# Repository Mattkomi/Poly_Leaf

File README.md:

# Poly_Leaf
PFE 2024-2025 Polytech SIR, projet Visio
Ce projet vise à développer un système de Stream Deck permettant de centraliser et d'optimiser la gestion des équipements situés dans des salles spécifiques. 
L'objectif est de créer un dispositif ergonomique et intuitif regroupant toutes les connexions HDMI, RJ45, et USB des différents équipements dans un système unifié, 
tout en offrant des fonctionnalités avancées comme la création de macros personnalisées.

Le système est conçu pour :

Simplifier la gestion des équipements grâce à une interface centralisée.
Automatiser des tâches fréquentes, comme l'affichage des participants sur l'écran de retour ou le lancement d'applications utilisées régulièrement.
Reproduire, tout en innovant, les fonctionnalités de l'interface StarLeaf.
Ce projet a été réalisé dans le cadre du PFE VISIO de la filière Polytech SIR par :

Vincent Goossens
Matthieu Komisarek

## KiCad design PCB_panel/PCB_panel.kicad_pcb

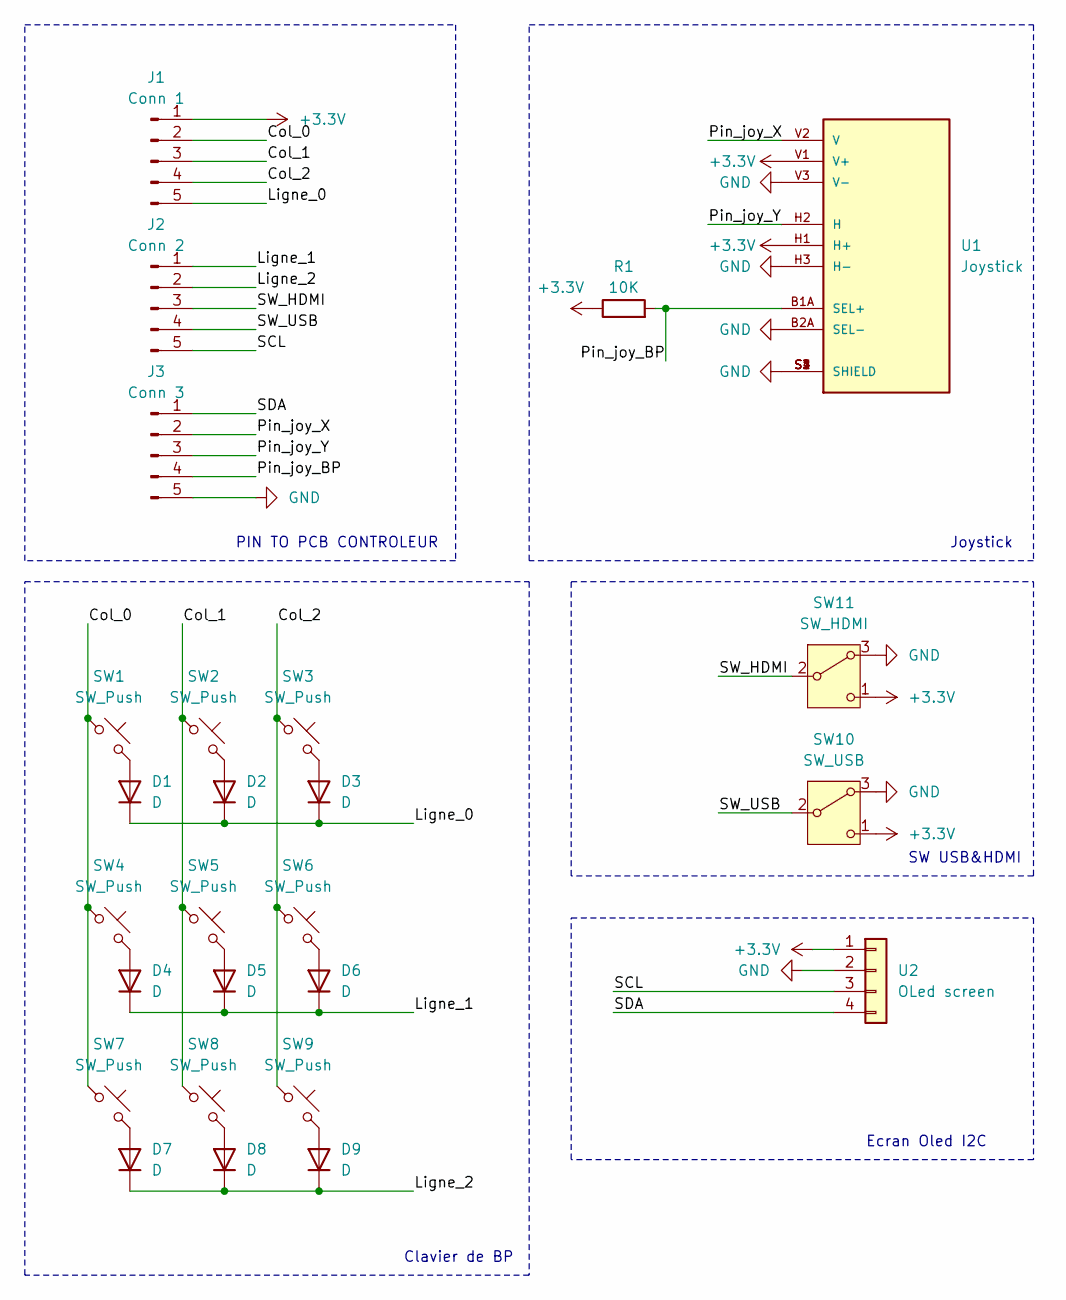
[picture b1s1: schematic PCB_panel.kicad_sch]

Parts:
D1, D2, D3, D4, D5, D6, D7, D8, D9: D; D_A-405_P10.16mm_Horizontal
J1: Conn 1; Molex_Micro-Fit_3.0_43650-0515_1x05_P3.00mm_Vertical
J2: Conn 2; Molex_Micro-Fit_3.0_43650-0515_1x05_P3.00mm_Vertical
J3: Conn 3; Molex_Micro-Fit_3.0_43650-0515_1x05_P3.00mm_Vertical
R1: 10K; R_Axial_DIN0207_L6.3mm_D2.5mm_P10.16mm_Horizontal
SW1, SW2, SW3, SW4, SW5, SW6, SW7, SW8, SW9: SW_Push; PVA1 OA H1 1.2N V2
SW10: SW_USB; PinHeader_1x03_P2.54mm_Vertical
SW11: SW_HDMI; PinHeader_1x03_P2.54mm_Vertical
U1: Joystick; XDCR_COM-09032; PARTREV N/A
U2: OLed screen; PinSocket_1x04_P2.54mm_Vertical

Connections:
+3.3V: J1.1, R1.1, SW10.1 (C), SW11.1 (C), U1.H1 (H+), U1.V1 (V+), U2.1
/Col_0: J1.2, SW1.1, SW4.1, SW7.1
/Col_1: J1.3, SW2.1, SW5.1, SW8.1
/Col_2: J1.4, SW3.1, SW6.1, SW9.1
/Ligne_0: D1.1 (K), D2.1 (K), D3.1 (K), J1.5
/Ligne_1: D4.1 (K), D5.1 (K), D6.1 (K), J2.1
/Ligne_2: D7.1 (K), D8.1 (K), D9.1 (K), J2.2
/Pin_joy_BP: J3.4, R1.2, U1.B1A (SEL+)
/Pin_joy_X: J3.2, U1.V2 (V)
/Pin_joy_Y: J3.3, U1.H2 (H)
/SCL: J2.5, U2.3
/SDA: J3.1, U2.4
/SW_HDMI: J2.3, SW11.2 (B)
/SW_USB: J2.4, SW10.2 (B)
GND: J3.5, SW10.3 (A), SW11.3 (A), U1.B2A (SEL-), U1.H3 (H-), U1.S1 (SHIELD), U1.S2 (SHIELD), U1.S3 (SHIELD), U1.S4 (SHIELD), U1.V3 (V-), U2.2
unnamed: D1.2 (A), SW1.2
unnamed: D2.2 (A), SW2.2
unnamed: D3.2 (A), SW3.2
unnamed: D4.2 (A), SW4.2
unnamed: D5.2 (A), SW5.2
unnamed: D6.2 (A), SW6.2
unnamed: D7.2 (A), SW7.2
unnamed: D8.2 (A), SW8.2
unnamed: D9.2 (A), SW9.2

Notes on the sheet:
Ecran Oled I2C
SW USB&HDMI
Joystick
PIN TO PCB CONTROLEUR
Clavier de BP

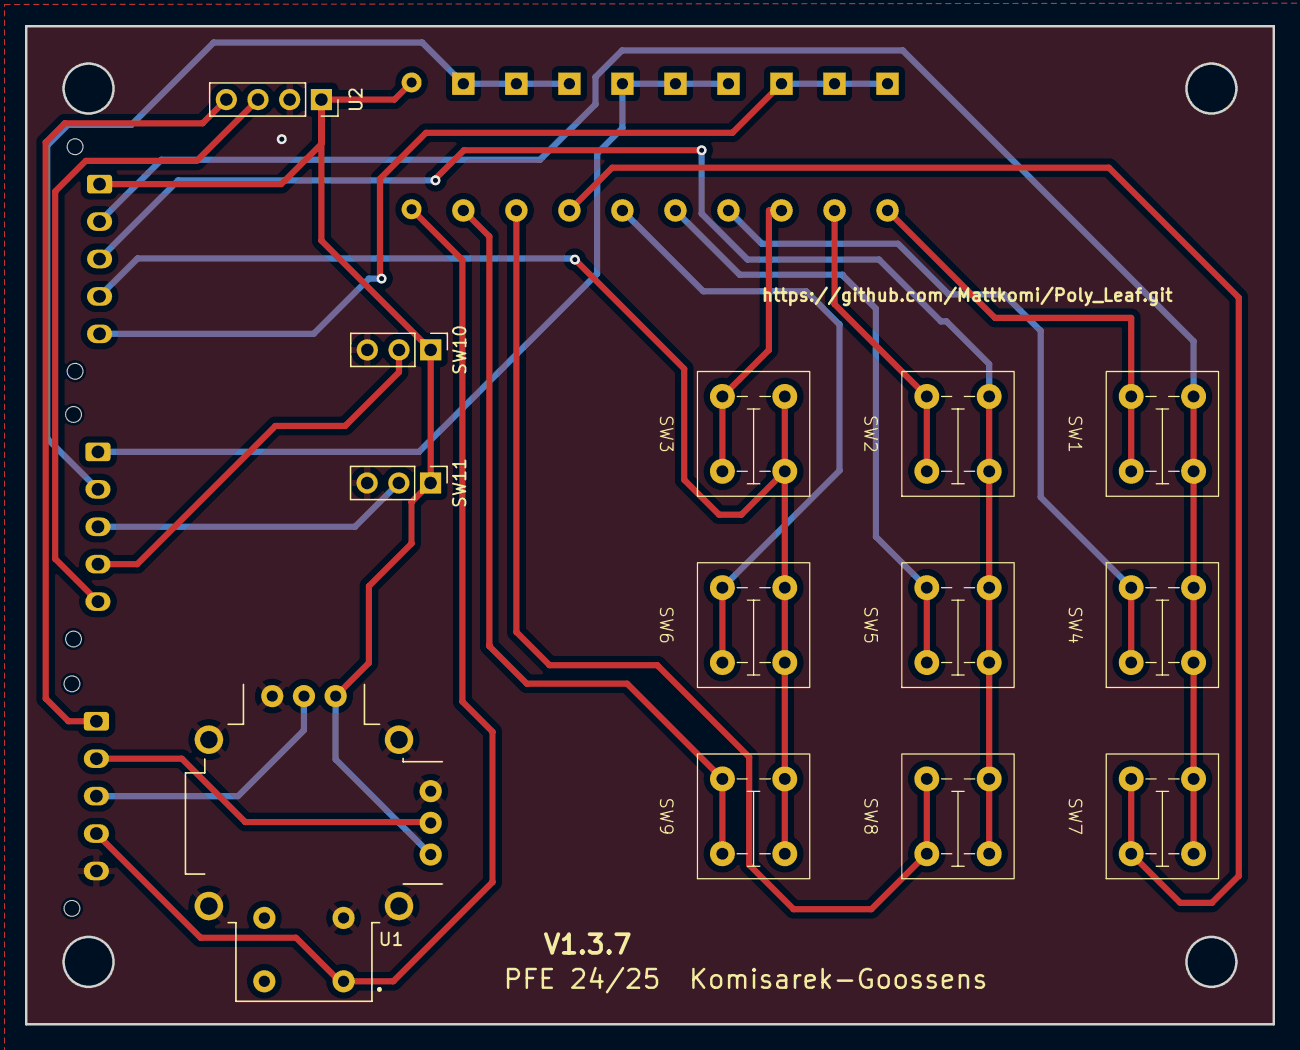
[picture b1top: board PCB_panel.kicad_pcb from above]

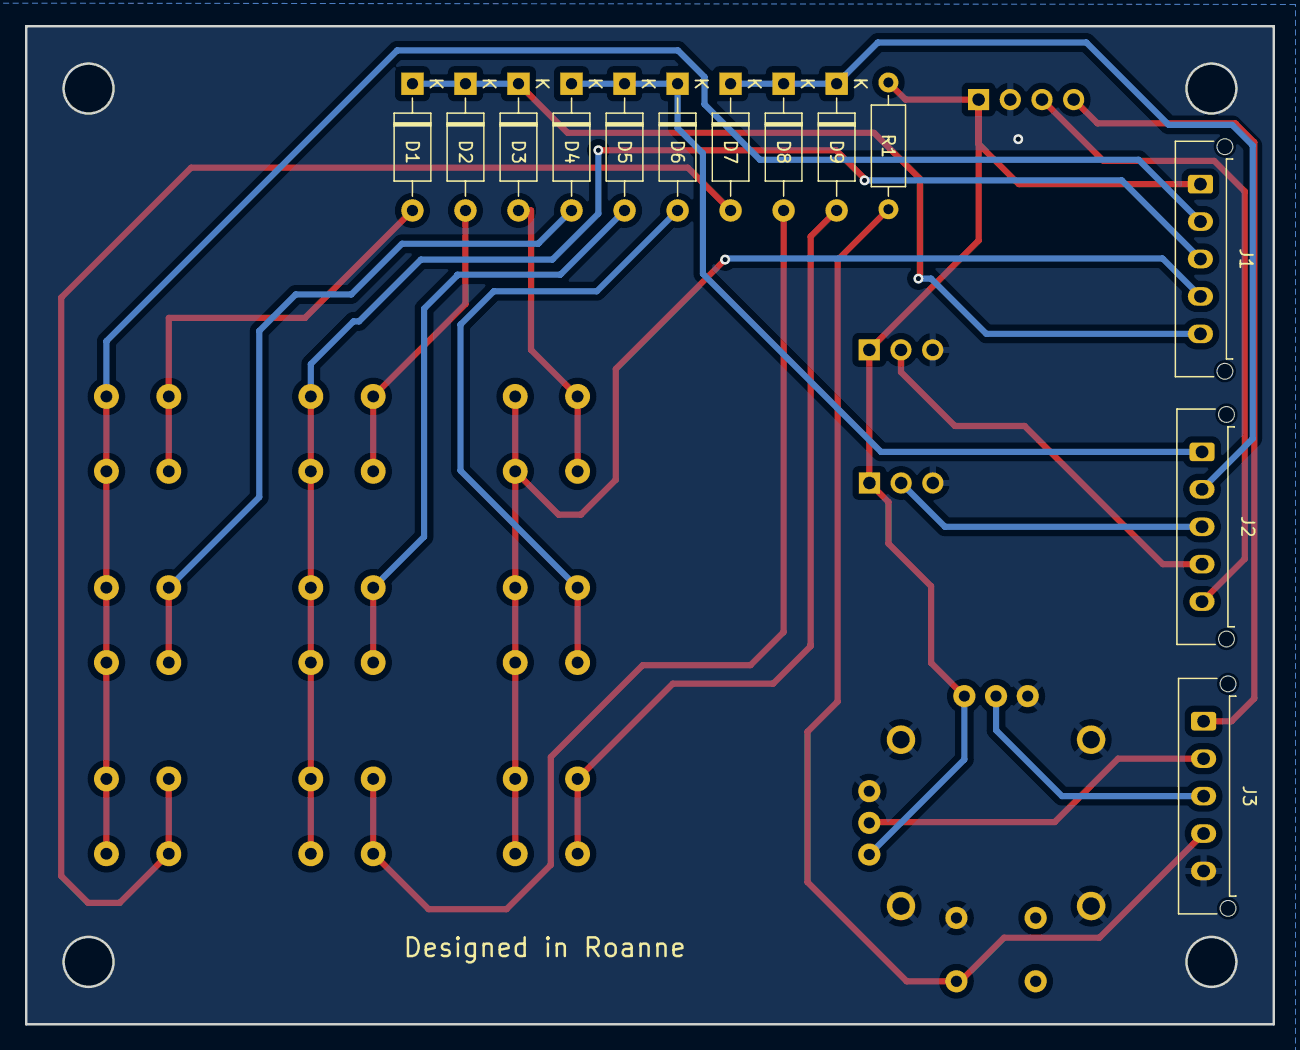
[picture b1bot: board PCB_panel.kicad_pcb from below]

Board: 2 copper layers, 100.0 x 80.0 mm, 26 parts (13 on the bottom side), 24 nets.

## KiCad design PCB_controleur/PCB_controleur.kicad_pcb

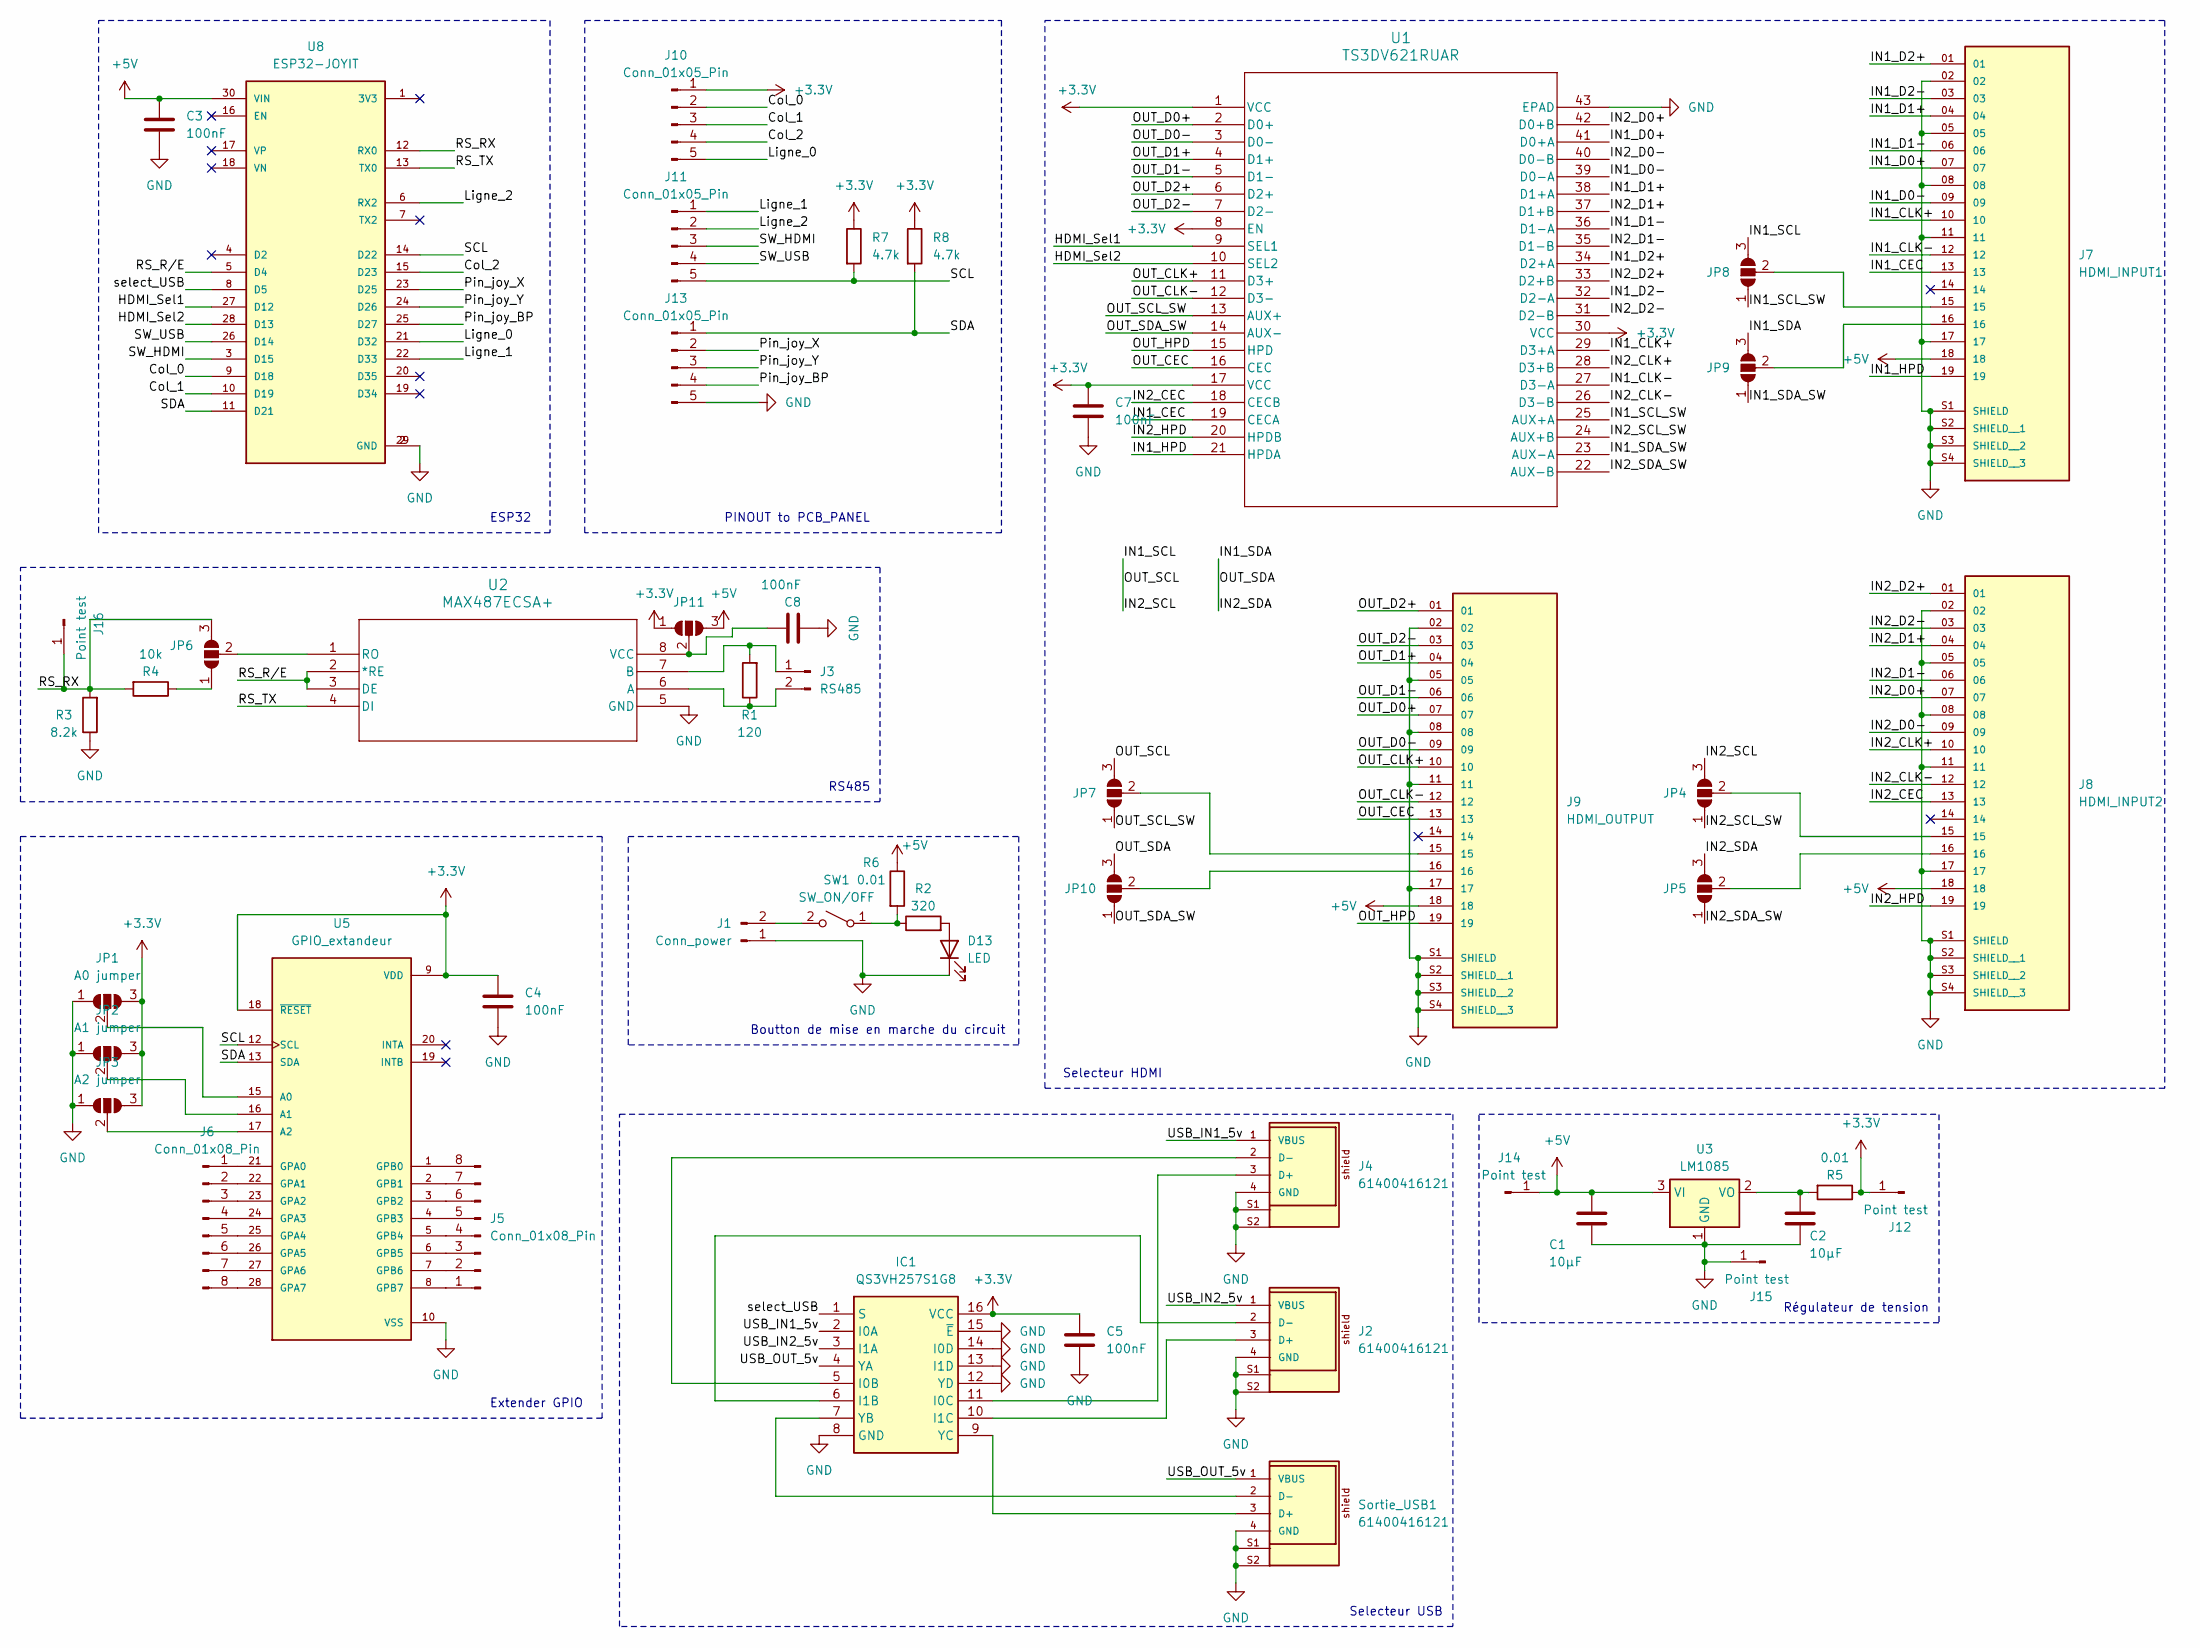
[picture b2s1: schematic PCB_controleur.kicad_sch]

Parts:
C1, C2: 10µF; CP_Radial_D5.0mm_P2.50mm
C3, C4, C5, C7, C8: 100nF; CAPC2012X135N
D13: LED; LED_D5.0mm
IC1: QS3VH257S1G8; SOIC127P600X175-16N; Manufacturer_Part_Number QS3VH257S1G8
J1: Conn_power; TerminalBlock_bornier-2_P5.08mm
J2, J4: 61400416121; PART-NUMBER 61400416121
J3: RS485; TerminalBlock_bornier-2_P5.08mm
J5, J6: Conn_01x08_Pin; PinHeader_1x08_P2.54mm_Vertical
J7: HDMI_INPUT1; SAMTEC_HDMR-19-01-S-SM-TR; PARTREV H
J8: HDMI_INPUT2; SAMTEC_HDMR-19-01-S-SM-TR; PARTREV H
J9: HDMI_OUTPUT; SAMTEC_HDMR-19-01-S-SM-TR; PARTREV H
J10, J11, J13: Conn_01x05_Pin; Molex_Micro-Fit_3.0_43650-0515_1x05_P3.00mm_Vertical
J12, J14, J15, J16: Point test; PinHeader_1x01_P2.00mm_Vertical
JP1: A0 jumper; SolderJumper-3_P1.3mm_Open_Pad1.0x1.5mm
JP2: A1 jumper; SolderJumper-3_P1.3mm_Open_Pad1.0x1.5mm
JP3: A2 jumper; SolderJumper-3_P1.3mm_Open_Pad1.0x1.5mm
JP4, JP5, JP6, JP7, JP8, JP9, JP10, JP11: SolderJumper_3_Open; SolderJumper-3_P1.3mm_Open_RoundedPad1.0x1.5mm_NumberLabels
R1: 120; R_Axial_DIN0207_L6.3mm_D2.5mm_P10.16mm_Horizontal
R2: 320; R_Axial_DIN0207_L6.3mm_D2.5mm_P10.16mm_Horizontal
R3: 8.2k; R_Axial_DIN0207_L6.3mm_D2.5mm_P10.16mm_Horizontal
R4: 10k; R_Axial_DIN0207_L6.3mm_D2.5mm_P10.16mm_Horizontal
R5, R6: 0.01; WSHM28181L000FEA
R7, R8: 4.7k; R_Axial_DIN0207_L6.3mm_D2.5mm_P10.16mm_Horizontal
SW1: SW_ON/OFF; JST_EH_B2B-EH-A_1x02_P2.50mm_Vertical
Sortie_USB1: 61400416121; 62900416021; PART-NUMBER 61400416121
U1: TS3DV621RUAR; RUA42_7P55X2P05_TEX
U2: MAX487ECSA+; 21-0041B_8_MXM
U3: LM1085; TO-220-3_Vertical
U5: GPIO_extandeur; SPDIP28_300MC_MCH; PARTREV C
U8: ESP32-JOYIT; MODULE_ESP32_DEVKIT_JOYIT; PARTREV N/A

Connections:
+3.3V: C4.1, C5.1, C7.1, IC1.16 (VCC), J10.1, J12.1, JP1.3 (B), JP2.3 (B), JP3.3 (B), JP11.1 (A), R5.1, R7.1, R8.1, U1.1 (VCC), U1.8 (EN), U1.17 (VCC), U1.30 (VCC), U5.9 (VDD), U5.18 (~RESET)
+5V: C1.1, C3.1, J7.18, J8.18, J9.18, J14.1, JP11.3 (B), R6.1, U3.3 (VI), U8.30 (VIN)
/Col_0: J10.2, U8.9 (D18)
/Col_1: J10.3, U8.10 (D19)
/Col_2: J10.4, U8.15 (D23)
/HDMI_Sel1: U1.9 (SEL1), U8.27 (D12)
/HDMI_Sel2: U1.10 (SEL2), U8.28 (D13)
/IN1_CEC: J7.13, U1.19 (CECA)
/IN1_CLK+: J7.10, U1.29 (D3+A)
/IN1_CLK-: J7.12, U1.27 (D3-A)
/IN1_D0+: J7.07, U1.41 (D0+A)
/IN1_D0-: J7.09, U1.39 (D0-A)
/IN1_D1+: J7.04, U1.38 (D1+A)
/IN1_D1-: J7.06, U1.36 (D1-A)
/IN1_D2+: J7.01, U1.34 (D2+A)
/IN1_D2-: J7.03, U1.32 (D2-A)
/IN1_HPD: J7.19, U1.21 (HPDA)
/IN1_SCL: JP4.3 (B), JP7.3 (B), JP8.3 (B)
/IN1_SCL_SW: JP8.1 (A), U1.25 (AUX+A)
/IN1_SDA: JP5.3 (B), JP9.3 (B), JP10.3 (B)
/IN1_SDA_SW: JP9.1 (A), U1.23 (AUX-A)
/IN2_CEC: J8.13, U1.18 (CECB)
/IN2_CLK+: J8.10, U1.28 (D3+B)
/IN2_CLK-: J8.12, U1.26 (D3-B)
/IN2_D0+: J8.07, U1.42 (D0+B)
/IN2_D0-: J8.09, U1.40 (D0-B)
/IN2_D1+: J8.04, U1.37 (D1+B)
/IN2_D1-: J8.06, U1.35 (D1-B)
/IN2_D2+: J8.01, U1.33 (D2+B)
/IN2_D2-: J8.03, U1.31 (D2-B)
/IN2_HPD: J8.19, U1.20 (HPDB)
/IN2_SCL_SW: JP4.1 (A), U1.24 (AUX+B)
/IN2_SDA_SW: JP5.1 (A), U1.22 (AUX-B)
/Ligne_0: J10.5, U8.21 (D32)
/Ligne_1: J11.1, U8.22 (D33)
/Ligne_2: J11.2, U8.6 (RX2)
/OUT_CEC: J9.13, U1.16 (CEC)
/OUT_CLK+: J9.10, U1.11 (D3+)
/OUT_CLK-: J9.12, U1.12 (D3-)
/OUT_D0+: J9.07, U1.2 (D0+)
/OUT_D0-: J9.09, U1.3 (D0-)
/OUT_D1+: J9.04, U1.4 (D1+)
/OUT_D1-: J9.06, U1.5 (D1-)
/OUT_D2+: J9.01, U1.6 (D2+)
/OUT_D2-: J9.03, U1.7 (D2-)
/OUT_HPD: J9.19, U1.15 (HPD)
/OUT_SCL_SW: JP7.1 (A), U1.13 (AUX+)
/OUT_SDA_SW: JP10.1 (A), U1.14 (AUX-)
/Pin_joy_BP: J13.4, U8.25 (D27)
/Pin_joy_X: J13.2, U8.23 (D25)
/Pin_joy_Y: J13.3, U8.24 (D26)
/RS_RX: J16.1, JP6.3 (B), R3.2, R4.2, U8.12 (RX0)
/RS_R/E: U2.2 (*RE), U2.3 (DE), U8.5 (D4)
/RS_TX: U2.4 (DI), U8.13 (TX0)
/SCL: J11.5, R7.2, U5.12 (SCL), U8.14 (D22)
/SDA: J13.1, R8.2, U5.13 (SDA), U8.11 (D21)
/SW_HDMI: J11.3, U8.3 (D15)
/SW_USB: J11.4, U8.26 (D14)
/USB_IN1_5v: IC1.2 (I0A), J4.1 (VBUS)
/USB_IN2_5v: IC1.3 (I1A), J2.1 (VBUS)
/USB_OUT_5v: IC1.4 (YA), Sortie_USB1.1 (VBUS)
/select_USB: IC1.1 (S), U8.8 (D5)
GND: C1.2, C2.2, C3.2, C4.2, C5.2, C7.2, C8.2, D13.1 (K), IC1.8 (GND), IC1.12 (YD), IC1.13 (I1D), IC1.14 (I0D), IC1.15 (~E), J1.1, J2.4 (GND), J2.S1, J2.S2, J4.4 (GND), J4.S1, J4.S2, J7.02, J7.05, J7.08, J7.11, J7.17, J7.S1 (SHIELD), J7.S2 (SHIELD__1), J7.S3 (SHIELD__2), J7.S4 (SHIELD__3), J8.02, J8.05, J8.08, J8.11, J8.17, J8.S1 (SHIELD), J8.S2 (SHIELD__1), J8.S3 (SHIELD__2), J8.S4 (SHIELD__3), J9.02, J9.05, J9.08, J9.11, J9.17, J9.S1 (SHIELD), J9.S2 (SHIELD__1), J9.S3 (SHIELD__2), J9.S4 (SHIELD__3), J13.5, J15.1, JP1.1 (A), JP2.1 (A), JP3.1 (A), R3.1, Sortie_USB1.4 (GND), Sortie_USB1.S1, Sortie_USB1.S2, U1.43 (EPAD), U2.5 (GND), U3.1 (GND), U5.10 (VSS), U8.2 (GND), U8.29 (GND)
unnamed: D13.2 (A), R2.2
unnamed: IC1.5 (I0B), J4.2 (D-)
unnamed: IC1.11 (I0C), J4.3 (D+)
unnamed: IC1.6 (I1B), J2.2 (D-)
unnamed: IC1.10 (I1C), J2.3 (D+)
unnamed: IC1.7 (YB), Sortie_USB1.2 (D-)
unnamed: IC1.9 (YC), Sortie_USB1.3 (D+)
unnamed: J1.2, SW1.2 (B)
unnamed: J3.1, R1.2, U2.7 (B)
unnamed: J3.2, R1.1, U2.6 (A)
unnamed: J5.1, U5.8 (GPB7)
unnamed: J5.2, U5.7 (GPB6)
unnamed: J5.3, U5.6 (GPB5)
unnamed: J5.4, U5.5 (GPB4)
unnamed: J5.5, U5.4 (GPB3)
unnamed: J5.6, U5.3 (GPB2)
unnamed: J5.7, U5.2 (GPB1)
unnamed: J5.8, U5.1 (GPB0)
unnamed: J6.1, U5.21 (GPA0)
unnamed: J6.2, U5.22 (GPA1)
unnamed: J6.3, U5.23 (GPA2)
unnamed: J6.4, U5.24 (GPA3)
unnamed: J6.5, U5.25 (GPA4)
unnamed: J6.6, U5.26 (GPA5)
unnamed: J6.7, U5.27 (GPA6)
unnamed: J6.8, U5.28 (GPA7)
unnamed: JP1.2 (C), U5.15 (A0)
unnamed: JP2.2 (C), U5.16 (A1)
unnamed: JP3.2 (C), U5.17 (A2)
unnamed: J8.15, JP4.2 (C)
unnamed: J8.16, JP5.2 (C)
unnamed: JP6.1 (A), R4.1
unnamed: JP6.2 (C), U2.1 (RO)
unnamed: J9.15, JP7.2 (C)
unnamed: J7.15, JP8.2 (C)
unnamed: J7.16, JP9.2 (C)
unnamed: J9.16, JP10.2 (C)
unnamed: C8.1, JP11.2 (C), U2.8 (VCC)
unnamed: R2.1, R6.2, SW1.1 (A)
unnamed: C2.1, R5.2, U3.2 (VO)

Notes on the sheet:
RS485
PINOUT to PCB_PANEL
Selecteur USB
Extender GPIO
ESP32
Selecteur HDMI
Régulateur de tension
Boutton de mise en marche du circuit

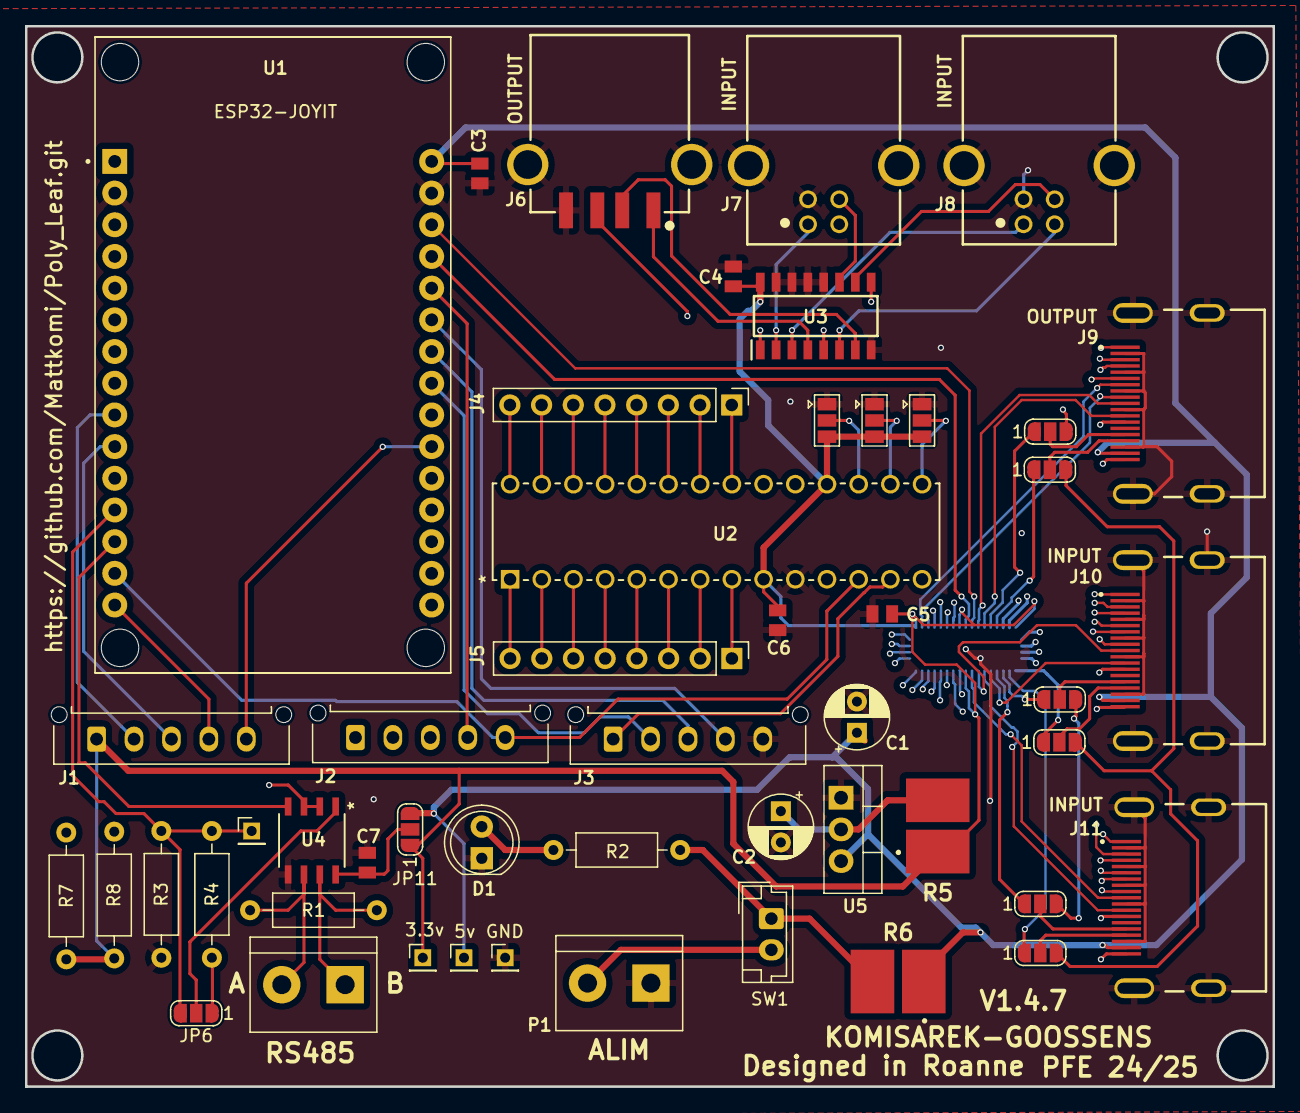
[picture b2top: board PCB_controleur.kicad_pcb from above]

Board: 4 copper layers, 100.0 x 85.0 mm, 51 parts (1 on the bottom side), 103 nets.

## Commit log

2024-11-28 PCB_PANEL_V1.3.1
2024-11-28 Add .step pcb_panel
2024-11-28 Components Datasheet
2024-11-28 Liste des composants V1.1.1
2025-02-10 Add test programme
2025-02-10 Programme de test
2025-02-12 Ajout du PCB Contrôleur
2025-02-12 CAO du projet
2025-02-18 update pcb
2025-02-19 Programme principal
